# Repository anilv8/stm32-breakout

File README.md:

# stm32-breakout
# Schematic of circuit

## ERC Result

# PCB Board
### Front Copper

### Back copper

## DRC Result

## 3D view of PCB
### Front:

### Back:

## Gerber
### Front Copper

### Back Copper

# BOM
| Item	| Qty	| Reference(s)	| Value	| LibPart	| Footprint	| Datasheet |
| ----- | ----- | ----- | ----- | ----- | ----- | ----- |
| 1	| 2	| C1, C2 |	1u	| Device:C |	Capacitor_SMD:C_0603_1608Metric |	~ |
| 2	| 1	| C3 |	4u7	| Device:C	| Capacitor_SMD:C_0603_1608Metric |	~ |
| 3 |	5 |	C4, C5, C6, C7, C9 |	100n |	Device:C	| Capacitor_SMD:C_0402_1005Metric |	~ |
| 4 |	1 |	C8 |	1u |	Device:C |	Capacitor_SMD:C_0402_1005Metric	| ~ |
| 5	| 2	| C10, C11	| 30p	| Device:C	| Capacitor_SMD:C_0402_1005Metric	| ~ |
| 6 |	1 |	D1	| GREEN |	Device:LED_Small |	LED_SMD:LED_0603_1608Metric |	~ |
| 7	| 1	| D2 |	BLUE	| Device:LED_Small	| LED_SMD:LED_0603_1608Metric |	~ |
| 8 |	1	| FB1	| 100R	| Device:FerriteBead	| Inductor_SMD:L_0805_2012Metric |	~ |
| 9 |	4	| H1, H2, H3, H4 |	MountingHole |	Mechanical:MountingHole	MountingHole:MountingHole_2.2mm_M2 |	~ |
| 10 | 1 |	J1 |	USB_B_Micro	| Connector:USB_B_Micro |	Connector_USB:USB_Micro-B_Wuerth_629105150521	| ~ |
| 11	| 2	| J2, J3 |	Conn_01x15	| Connector_Generic:Conn_01x15	| Connector_PinHeader_2.54mm:PinHeader_1x15_P2.54mm_Vertical	| ~ |
| 12 |	1	| JP1	| SolderJumper_2_Open |	Jumper:SolderJumper_2_Open	| Jumper:SolderJumper-2_P1.3mm_Open_Pad1.0x1.5mm |	~ |
| 13	| 1	| L1	| 27n |	Device:L	| Inductor_SMD:L_0402_1005Metric | ~ |
| 14 |	2 |	R1, R3	| 1k5 |	Device:R |	Resistor_SMD:R_0603_1608Metric	| ~ |
| 15	| 1	| R2	| 10k	| Device:R	| Resistor_SMD:R_0402_1005Metric	| ~ |
| 16 |	1 |	R4	| 1k5	| Device:R |	Resistor_SMD:R_0402_1005Metric |	~ |
| 17 | 1	| U1	| XC6206P333MR	| Regulator_Linear:XC6206PxxxMR	| Package_TO_SOT_SMD:SOT-23-3	| https://www.torexsemi.com/file/xc6206/XC6206.pdf |
| 18	| 1 | U2	| STM32F103C8Tx	| MCU_ST_STM32F1:STM32F103C8Tx	| Package_QFP:LQFP-48_7x7mm_P0.5mm |	https://www.st.com/resource/en/datasheet/stm32f103c8.pdf |
| 19 |	1|	Y1 |	8MHz	| Device:Crystal_Small	| Crystal:Crystal_SMD_5032-2Pin_5.0x3.2mm	| ~ |

# REFERENCES
[1]  https://www.youtube.com/watch?v=wLwKgMBWhpY

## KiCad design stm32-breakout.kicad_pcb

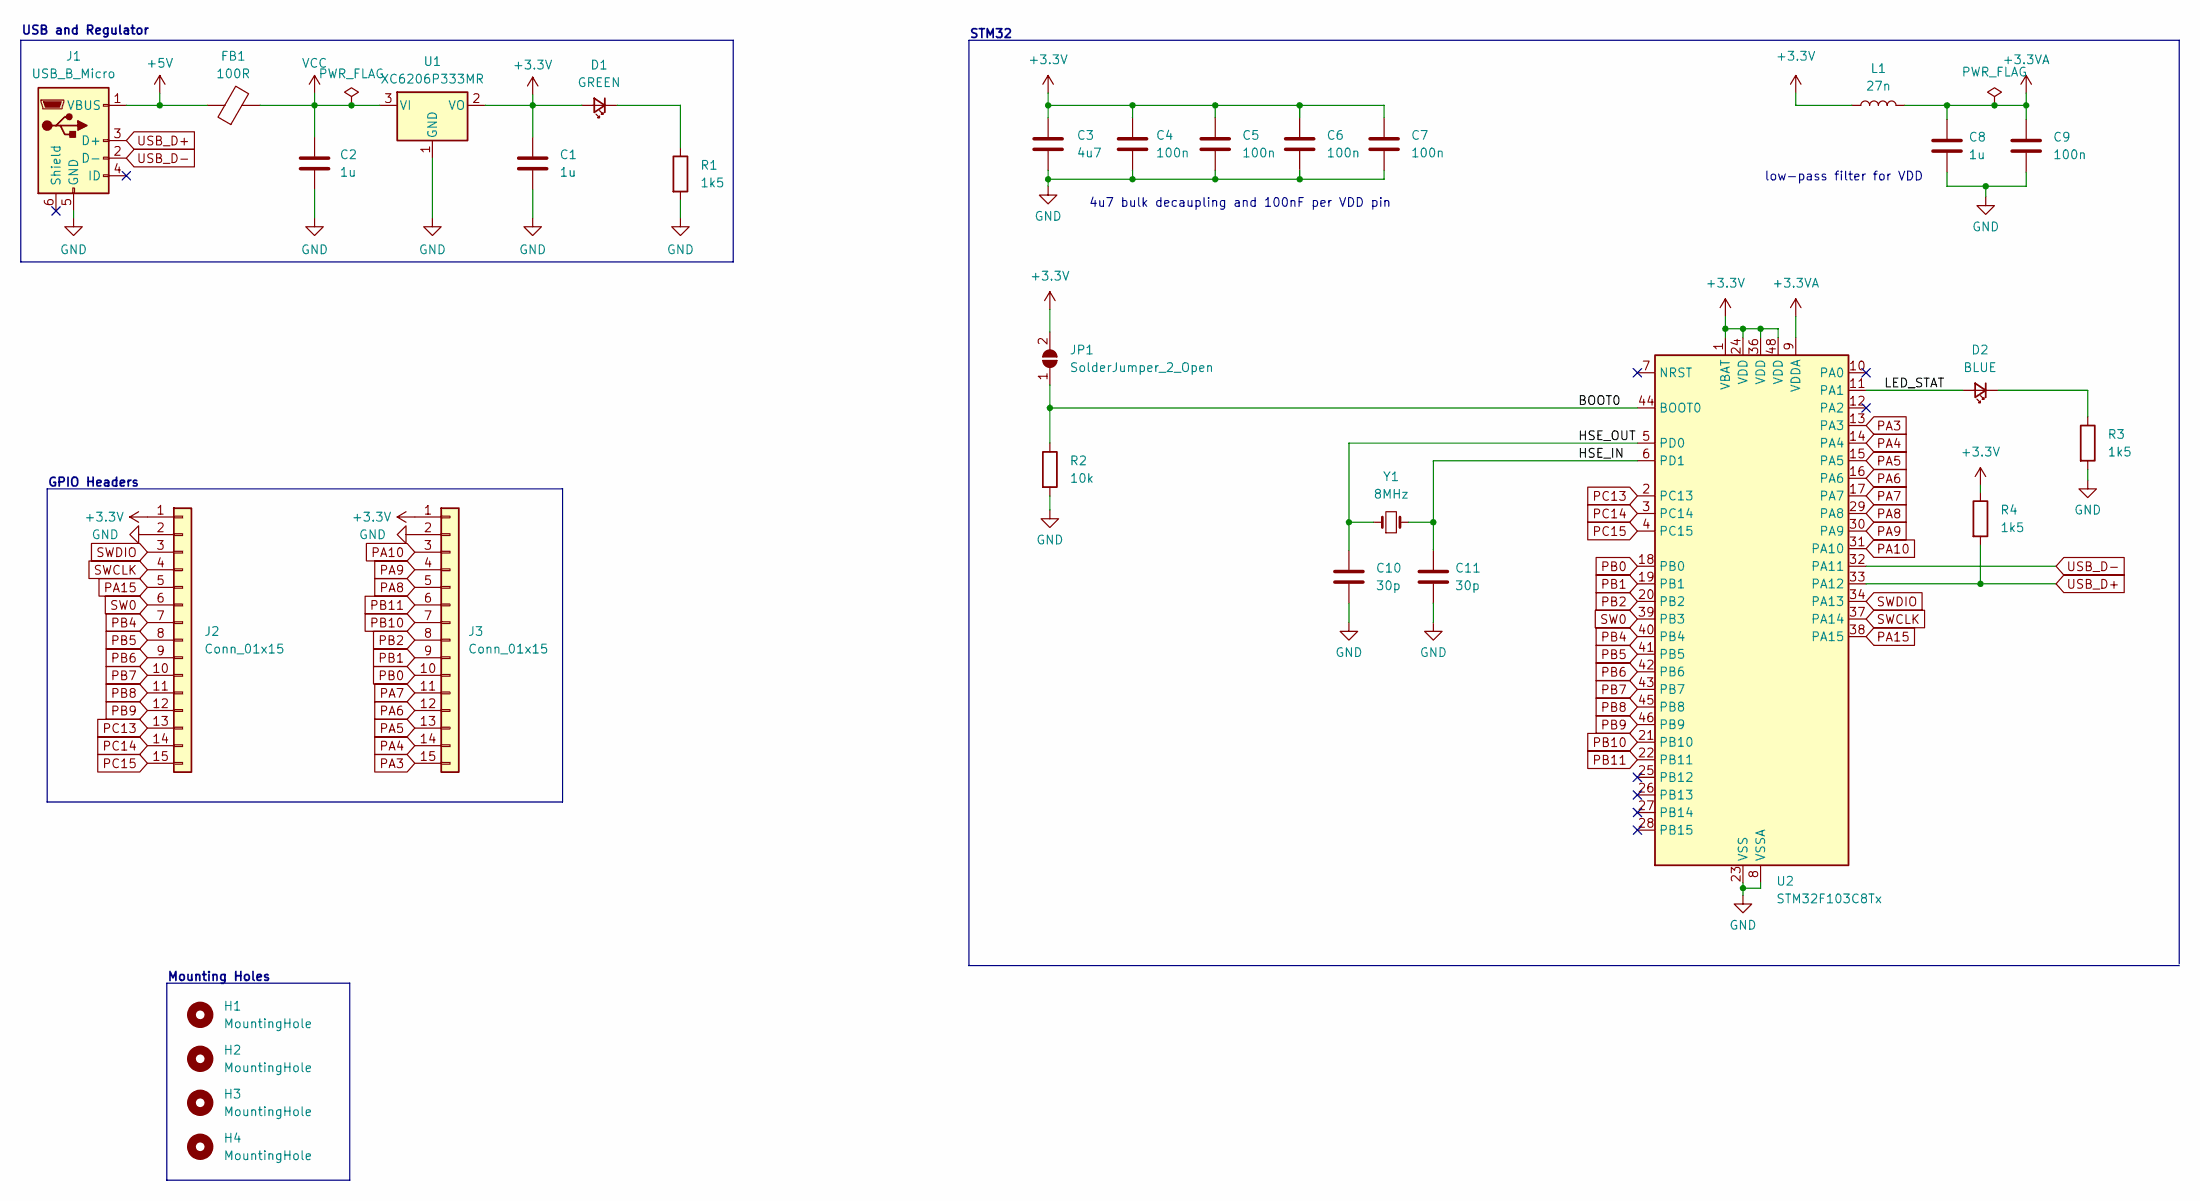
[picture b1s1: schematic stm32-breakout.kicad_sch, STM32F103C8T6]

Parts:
C1, C2: 1u; C_0603_1608Metric
C3: 4u7; C_0603_1608Metric
C4, C5, C6, C7, C9: 100n; C_0402_1005Metric
C8: 1u; C_0402_1005Metric
C10, C11: 30p; C_0402_1005Metric
D1: GREEN; LED_0603_1608Metric
D2: BLUE; LED_0603_1608Metric
FB1: 100R; L_0805_2012Metric
H1, H2, H3, H4: MountingHole; MountingHole_2.2mm_M2
J1: USB_B_Micro; USB_Micro-B_Wuerth_629105150521
J2, J3: Conn_01x15; PinHeader_1x15_P2.54mm_Vertical
JP1: SolderJumper_2_Open; SolderJumper-2_P1.3mm_Open_Pad1.0x1.5mm
L1: 27n; L_0402_1005Metric
R1, R3: 1k5; R_0603_1608Metric
R2: 10k; R_0402_1005Metric
R4: 1k5; R_0402_1005Metric
U1: XC6206P333MR; SOT-23-3
U2: STM32F103C8Tx; LQFP-48_7x7mm_P0.5mm
Y1: 8MHz; Crystal_SMD_5032-2Pin_5.0x3.2mm

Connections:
+3.3V: C1.1, C3.1, C4.1, C5.1, C6.1, C7.1, D1.2 (A), J2.1, J3.1, JP1.2 (B), L1.1, R4.1, U1.2 (VO), U2.1 (VBAT), U2.24 (VDD), U2.36 (VDD), U2.48 (VDD)
+3.3VA: C8.1, C9.1, L1.2, U2.9 (VDDA)
+5V: FB1.1, J1.1 (VBUS)
/BOOT0: JP1.1 (A), R2.1, U2.44 (BOOT0)
/HSE_IN: C11.1, U2.6 (PD1), Y1.2
/HSE_OUT: C10.1, U2.5 (PD0), Y1.1
/LED_STAT: D2.2 (A), U2.11 (PA1)
GND: C1.2, C2.2, C3.2, C4.2, C5.2, C6.2, C7.2, C8.2, C9.2, C10.2, C11.2, J1.5 (GND), J2.2, J3.2, R1.2, R2.2, R3.2, U1.1 (GND), U2.8 (VSSA), U2.23 (VSS), U2.35 (VSS), U2.47 (VSS)
unnamed: D1.1 (K), R1.1
unnamed: D2.1 (K), R3.1
PA3: J3.15, U2.13 (PA3)
PA4: J3.14, U2.14 (PA4)
PA5: J3.13, U2.15 (PA5)
PA6: J3.12, U2.16 (PA6)
PA7: J3.11, U2.17 (PA7)
PA8: J3.5, U2.29 (PA8)
PA9: J3.4, U2.30 (PA9)
PA10: J3.3, U2.31 (PA10)
PA15: J2.5, U2.38 (PA15)
PB0: J3.10, U2.18 (PB0)
PB1: J3.9, U2.19 (PB1)
PB2: J3.8, U2.20 (PB2)
PB4: J2.7, U2.40 (PB4)
PB5: J2.8, U2.41 (PB5)
PB6: J2.9, U2.42 (PB6)
PB7: J2.10, U2.43 (PB7)
PB8: J2.11, U2.45 (PB8)
PB9: J2.12, U2.46 (PB9)
PB10: J3.7, U2.21 (PB10)
PB11: J3.6, U2.22 (PB11)
PC13: J2.13, U2.2 (PC13)
PC14: J2.14, U2.3 (PC14)
PC15: J2.15, U2.4 (PC15)
SW0: J2.6, U2.39 (PB3)
SWCLK: J2.4, U2.37 (PA14)
SWDIO: J2.3, U2.34 (PA13)
USB_D+: J1.3 (D+), R4.2, U2.33 (PA12)
USB_D-: J1.2 (D-), U2.32 (PA11)
VCC: C2.1, FB1.2, U1.3 (VI)

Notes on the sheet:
Mounting Holes
STM32
USB and Regulator
GPIO Headers
low-pass filter for VDD
4u7 bulk decaupling and 100nF per VDD pin

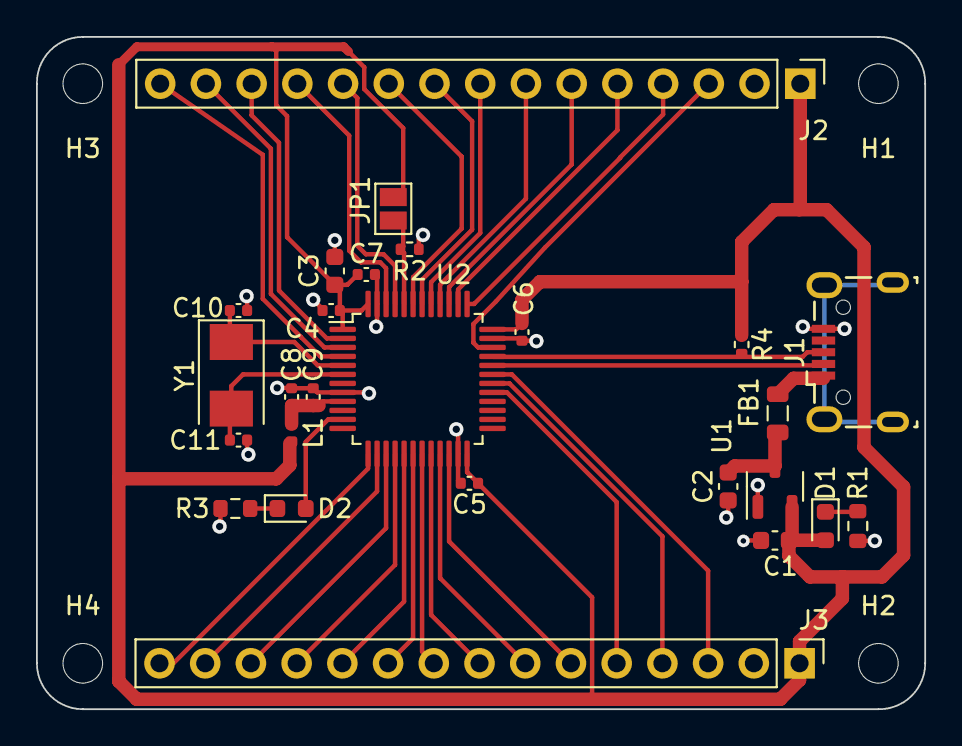
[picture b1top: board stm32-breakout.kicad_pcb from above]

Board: 2 copper layers, 49.3 x 37.3 mm, 30 parts (0 on the bottom side), 39 nets.
